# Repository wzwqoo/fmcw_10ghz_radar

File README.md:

# 10 GHz FMCW Radar Sensing Platform

A single-board **1TX / 3RX, 10 GHz FMCW radar**, its **Artix-7 range–Doppler–CFAR
backend**, and the **carrier board** that mounts the radar alongside a
pair of global-shutter cameras and an impact microphone.

The target application is a golf launch monitor: recover a ball's speed, launch
direction, spin rate and spin axis from radar and camera data. That
application drives every architectural choice here — three non-collinear
receivers (the minimum that gives a radar-native spin axis), per-receiver
*complex* range–Doppler maps published to DDR3 (the phase the spin-axis
interferometer consumes), and a once-per-shot Ethernet offload so the heavy
post-processing runs on a host PC instead of in fabric.

## Repository structure

| Path | Subsystem |
|---|---|
| [`rf_frontend/`](rf_frontend/) | The 10 GHz 1TX/3RX FMCW front-end: KiCad schematics and PCB on Isola 370HR |
| [`fpga/`](fpga/) | Artix-7 gateware: the raw-ADC → range–Doppler → CFAR pipeline, the DDR-to-host UDP offload path, MicroBlaze firmware, and the simulation stack |
| [`carrier_board/`](carrier_board/) | The carrier PCB that ties two cameras, radar, the FPGA module, Ethernet and audio together |

Each subsystem has its own README with the detail; the tables below are the map.

### `rf_frontend/` — 10 GHz FMCW front-end

A closed-loop fractional-N ramp PLL (ADF4159) drives a 10 GHz VCO (HMC1163)
across a 192 MHz sweep in 108 µs. A branchline coupler and a 3-way Wilkinson
tree supply a coherent LO to three
LNA-first receive chains (PMA3-14LN+ → LTC5548 → ADA4940-2), which land on an
ADAR7251's simultaneously-sampled channels. The antennas are series-fed patch
columns arranged in a staggered "^", stepped λ/2 between adjacent phase centres
in both array axes, so per-Doppler-bin angles never wrap.

→ [`rf_frontend/README.md`](rf_frontend/README.md)

### `fpga/` — Artix-7 digital backend

`01_adar7251_ppi_rx` → TDM mux → band-pass + Hilbert FIR → per-RX range FFT →
transposed DDR scatter (region A) → Doppler sequencer → per-RX Doppler FFT →
non-coherent integration (region C) + per-RX complex cache (region B) →
streaming cell-averaging CFAR (region D). A 128 × 256 grid, double-buffered so
software never reads a torn frame. An audio-plus-speed trigger picks the first
frame after impact that clears both gates and dumps its B/C/D regions to the
host over UDP.

→ [`fpga/README.md`](fpga/README.md)

### `carrier_board/` — camera + radar carrier

The routed six-layer carrier connects two OV9281 cameras through MC20901
bridges, the radar through a 40-pin FPC, and the Artix-7 module through two
140-pin B2B connectors. It also carries I²S audio, Gigabit Ethernet, and the
power tree.

→ [`carrier_board/README.md`](carrier_board/README.md)

## Status

| Item | State |
|---|---|
| `rf_frontend/` schematics + PCB layout | Routed KiCad project; board validation remains open |
| `fpga/` RTL pipeline (`01`…`08`) | Complete; unit tests and a raw-ADC-to-CFAR xsim run against the real Xilinx FFT/FIR IP |
| `fpga/` host offload (streamer, packetizer, receiver) | Complete and unit-tested |
| `fpga/firmware/audio_dsp.c` | Complete |
| `fpga/firmware/fusion_control.c` | **Work in progress** — the audio + speed trigger FSM and its frame-selection policy are still being written |
| `carrier_board/ov9281/` | Routed KiCad project; camera fit and board bring-up remain open |

## Toolchain

| Tool | Used for |
|---|---|
| KiCad 10 | `rf_frontend/kicad/`, `carrier_board/ov9281/` |
| Vivado 2025.1 | Block design, IP generation, synthesis, the xsim end-to-end run |
| Icarus Verilog | The RTL unit tests — they need no vendor IP (`fpga/sim/run_unit_tests.sh`) |
| Python 3 (numpy, matplotlib) | Stimulus generation, CFAR golden checks, the UDP frame receiver |
| FreeCAD | Archived IMX477 lens holder in `carrier_board/archive/imx477/mechanical/` |

Large generated trees are deliberately out of the repository: the Vivado
project's `.runs`/`.gen`/`.cache` output, xsim build directories, and the ADS
and HFSS workspaces.

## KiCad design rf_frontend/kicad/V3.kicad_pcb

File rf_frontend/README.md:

# `rf_frontend/` — 10 GHz 1TX/3RX FMCW front-end

The analog half of the platform: a coherent FMCW radar that sweeps 192 MHz
around 10 GHz in 108 µs, radiates it from a series-fed patch column, and lands
three receive chains on an ADAR7251's simultaneously-sampled ADC channels.
Simultaneous sampling is the point — it is what preserves the inter-receiver
phase that angle-of-arrival and the spin-axis interferometer downstream consume.

Everything is discrete MMIC rather than an integrated transceiver, so each
channel's gain, noise figure and LO drive is set and measurable on its own.

## Signal chain

## Key components

| Function | Part |
|---|---|
| Ramp PLL (fractional-N, type 2) | ADF4159 |
| VCO, 10 GHz fundamental + ÷2 | HMC1163 |
| Loop-filter amplifier (JFET input) | ADA4625-1 |
| Reference oscillator / buffer | KT2520K, NB3N551 |
| LNA, ×3 | PMA3-14LN+ |
| Downconversion mixer, ×3 | LTC5548 |
| Differential IF driver | ADA4940-2 |
| ADC — 4 channels, simultaneous sampling | ADAR7251 |
| LO distribution | LO-favor branchline coupler + 3-way Wilkinson with two 75 Ω isolation resistors + phase-trimmed arms (all distributed, on-board) |
| Pad attenuators | PAT1220 (4 dB / 6 dB) |
| Supplies | TPS7A4701 and TPS7A91 (low-noise LDO for the RF rails), TPS54302, MIC29302A, ADP1613 boost |
| Host interface | 40-pin shielded FPC to the carrier board |

## Antenna array

Three receive columns and one transmit column use series-fed patches on the
top layer. Ground cutouts and stitched feed transitions connect the columns
to the RF front-end.

## Substrate

Four-layer Isola 370HR, with the RF routing referenced to In1 and the antenna
columns over In2.

## Layout

| Path | Contents |
|---|---|
| `kicad/V3.kicad_pro`, `V3.kicad_sch` | KiCad project and top-level sheet |
| `kicad/TX.kicad_sch` | VCO, ramp PLL, loop filter, coupler, LO tree, TX feed |
| `kicad/RX.kicad_sch` | 3× LNA → mixer receive chains |
| `kicad/IF.kicad_sch` | IF conditioning and the ADAR7251 |
| `kicad/power.kicad_sch` | Power tree, with the RF rails on low-noise LDOs |
| `kicad/V3.kicad_pcb`, `V3.kicad_dru` | Board layout and custom DRC rules (net classes, input-path width) |
| `kicad/Design1.pll`, `Design2.pll` | ADIsimPLL loop designs |
| `kicad/footprints/` | Project-local libraries — including the hand-drawn `antenna`, `splitter` and `branchline` distributed structures |
| `figures/` | Link budget and board render |

The distributed structures are *footprints*, not components: the patch column,
the Wilkinson splitter and the branchline coupler are drawn as copper in
`kicad/footprints/*.pretty` and placed like parts.

## Status

The routed KiCad design is included. Board validation remains open.

## Opening the board

```
kicad rf_frontend/kicad/V3.kicad_pro     # KiCad 10
```

The render at the top of this page was produced with `kicad-cli pcb render`.

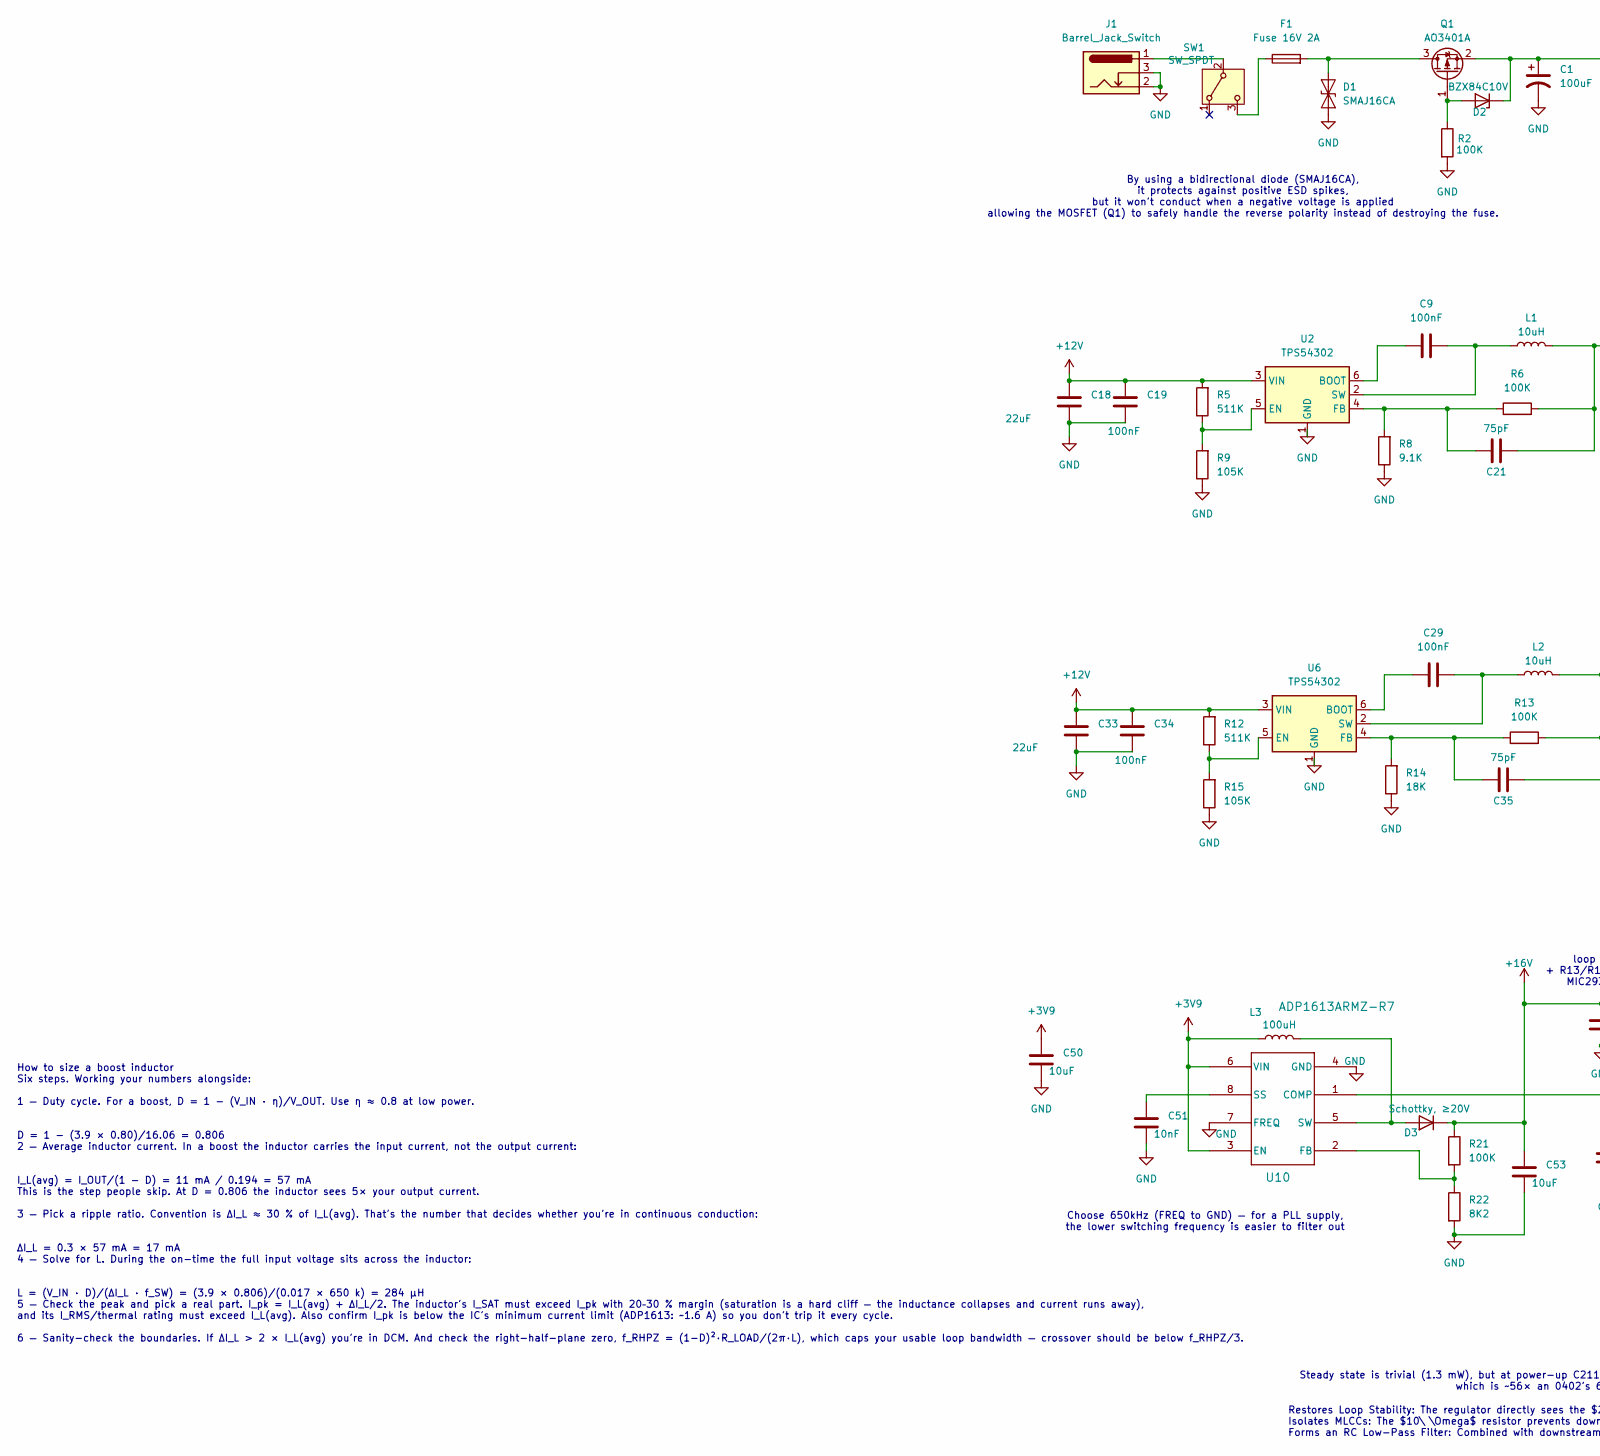
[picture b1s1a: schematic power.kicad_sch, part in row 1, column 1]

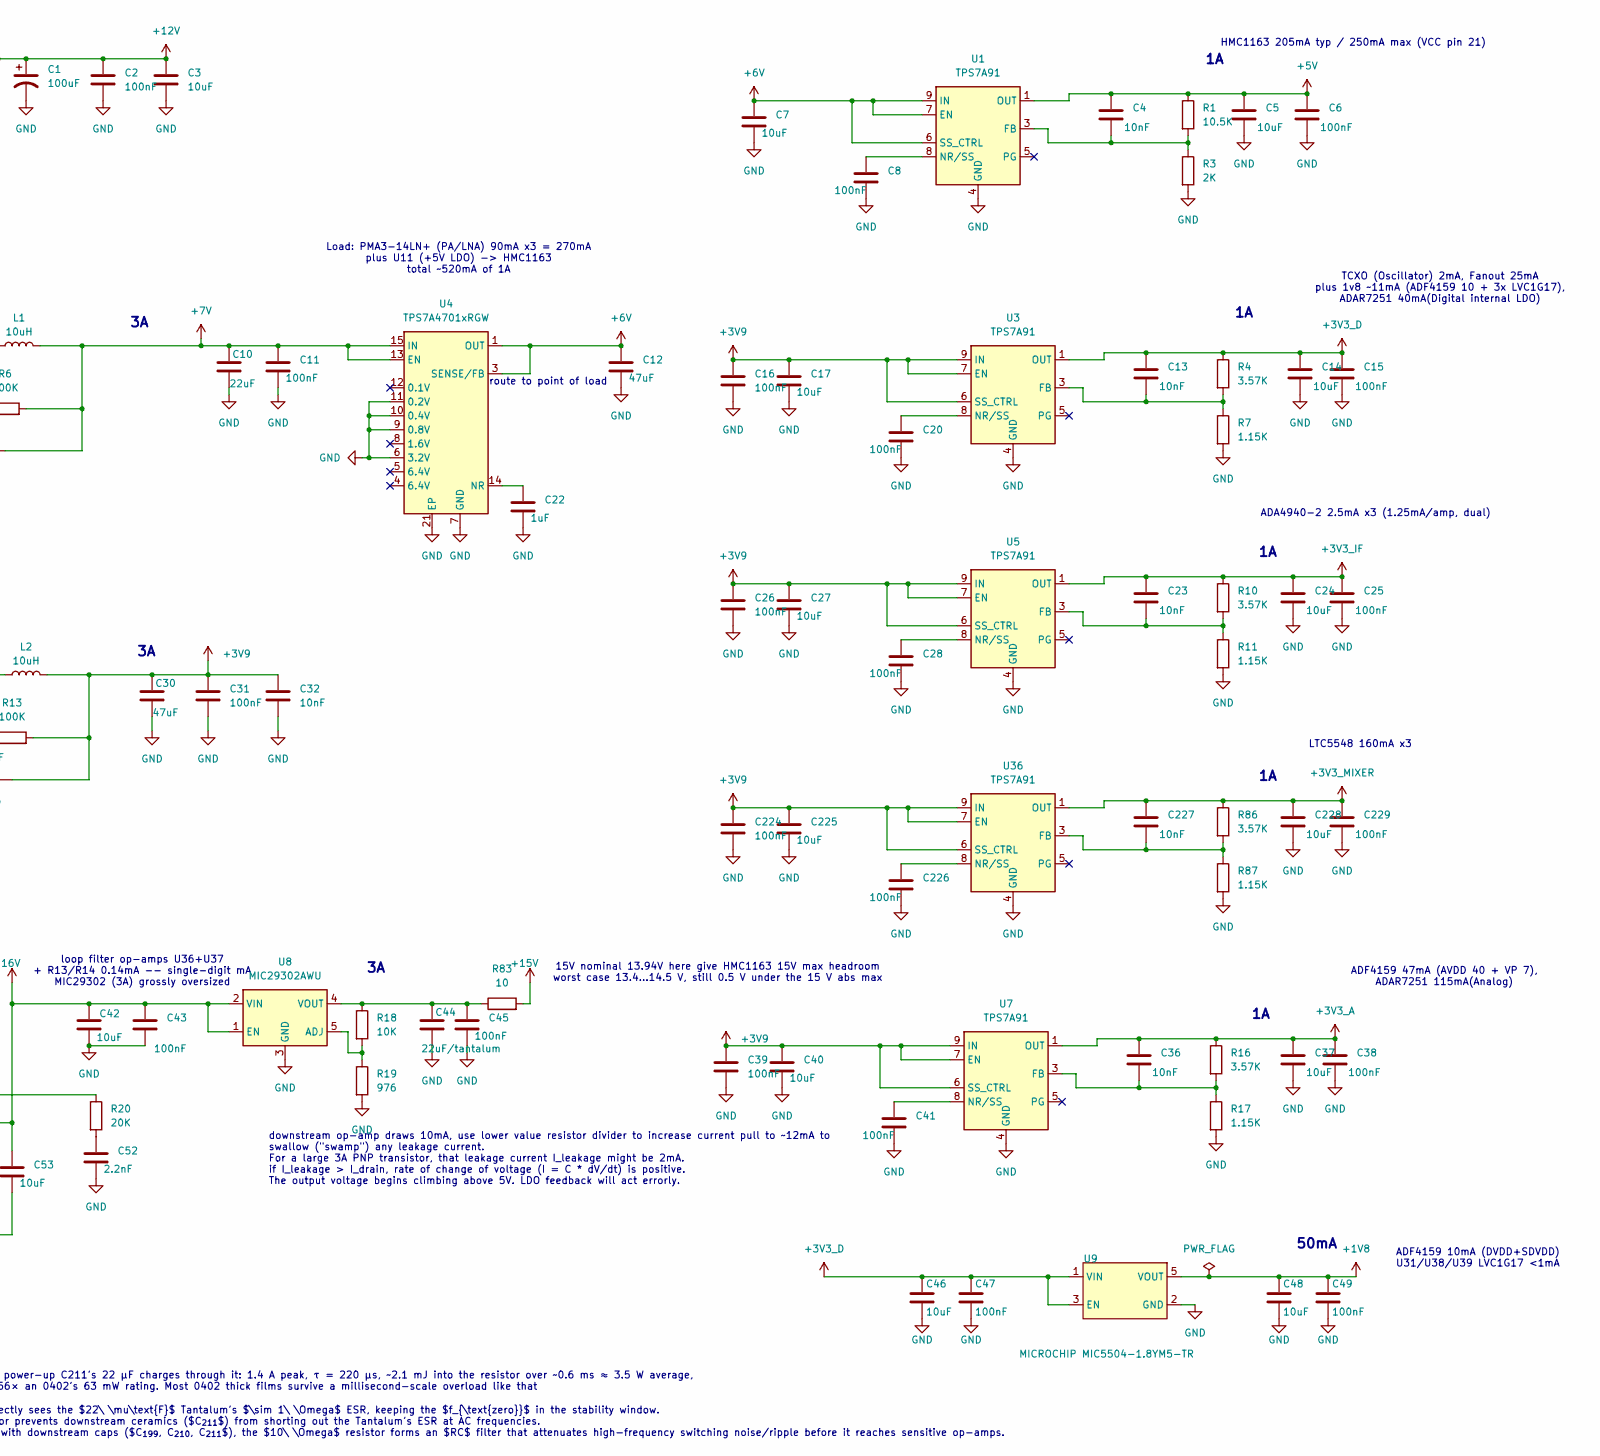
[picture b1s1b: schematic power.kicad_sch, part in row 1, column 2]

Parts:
C1: 100uF; CAPC6153X670N
C2, C6, C8, C9, C11, C15, C16, C19, C20, C25, C26, C28, C29, C31, C34, C38, C39, C41, C43, C45, C47, C49, C224, C226, C229: 100nF; C_0402_1005Metric
C3, C5, C7, C14, C17, C24, C27, C37, C40, C42, C46, C48, C50, C53, C225, C228: 10uF; C_0805_2012Metric
C4, C13, C23, C32, C36, C51, C227: 10nF; C_0402_1005Metric
C10, C18, C33: 22uF; C_0805_2012Metric
C12, C30: 47uF; C_0805_2012Metric
C21, C35: 75pF; C_0402_1005Metric
C22: 1uF; C_0402_1005Metric
C44: 22uF/tantalum; CP_EIA-6032-28_Kemet-C
C52: 2.2nF; C_0402_1005Metric
D1: SMAJ16CA; D_SMA
D2: BZX84C10V; SOT-23
D3: Schottky, ≥20V; D_SMA
F1: Fuse 16V 2A; Fuse_1812_4532Metric; LCSC Part # SMD1812P200TF16
J1: Barrel_Jack_Switch; BarrelJack_CUI_PJ-063AH_Horizontal
L1, L2: 10uH; L_Sunlord_MWSA0602S; Part# FXL0630-100-M
L3: 100uH; L_TechFuse_SL0620
Q1: AO3401A; SOT-23
R1: 10.5K; R_0402_1005Metric
R2, R6, R13, R21: 100K; R_0402_1005Metric
R3: 2K; R_0402_1005Metric
R4, R10, R16, R86: 3.57K; R_0402_1005Metric
R5, R12: 511K; R_0402_1005Metric
R7, R11, R17, R87: 1.15K; R_0402_1005Metric
R8: 9.1K; R_0402_1005Metric
R9, R15: 105K; R_0402_1005Metric
R14: 18K; R_0402_1005Metric
R18: 10K; R_0402_1005Metric
R19: 976; R_0402_1005Metric
R20: 20K; R_0402_1005Metric
R22: 8K2; R_0402_1005Metric
R83: 10; R_0603_1608Metric
SW1: SW_SPDT; SW-TH_3P-L12.7-W6.6-P4.70_C9900034369; Part# SS-12D10-G090; LCSC Part # C5155552
U1, U3, U5, U7, U36: TPS7A91; Texas_S-PDSO-N10_EP1.2x2mm
U2, U6: TPS54302; SOT-23-6
U4: TPS7A4701xRGW; Texas_RGW0020A_VQFN-20-1EP_5x5mm_P0.65mm_EP3.15x3.15mm
U8: MIC29302AWU; TO-263-5_TabPin3
U9: MICROCHIP MIC5504-1.8YM5-TR; SOT-23-5; Part# MIC5504-1.8YM5-TR; LCSC Part # C626116
U10: ADP1613ARMZ-R7; MSOP-8-1EP_3x3mm_P0.65mm_EP1.5x1.8mm

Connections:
+1V8: C48.1, C49.1, U9.5 (VOUT); also elsewhere on the board
+3V3_A: C36.1, C37.1, C38.1, R16.1, U7.1 (OUT), U7.2 (OUT); also elsewhere on the board
+3V3_D: C13.1, C14.1, C15.1, C46.1, C47.1, R4.1, U3.1 (OUT), U3.2 (OUT), U9.1 (VIN), U9.3 (EN); also elsewhere on the board
+3V3_IF: C23.1, C24.1, C25.1, R10.1, U5.1 (OUT), U5.2 (OUT); also elsewhere on the board
+3V3_MIXER: C227.1, C228.1, C229.1, R86.1, U36.1 (OUT), U36.2 (OUT); also elsewhere on the board
+3V9: C16.1, C17.1, C26.1, C27.1, C30.1, C31.1, C32.1, C35.2, C39.1, C40.1, C50.1, C224.1, C225.1, L2.2, L3.1, R13.2, U3.6 (SS_CTRL), U3.7 (EN), U3.9 (IN), U3.10 (IN), U5.6 (SS_CTRL), U5.7 (EN), U5.9 (IN), U5.10 (IN), U7.6 (SS_CTRL), U7.7 (EN), U7.9 (IN), U7.10 (IN), U10.3 (EN), U10.6 (VIN), U36.6 (SS_CTRL), U36.7 (EN), U36.9 (IN), U36.10 (IN)
+5V: C4.1, C5.1, C6.1, R1.1, U1.1 (OUT), U1.2 (OUT); also elsewhere on the board
+6V: C7.1, C12.1, U1.6 (SS_CTRL), U1.7 (EN), U1.9 (IN), U1.10 (IN), U4.1 (OUT), U4.3 (SENSE/FB), U4.20 (OUT); also elsewhere on the board
+7V: C10.1, C11.1, C21.2, L1.2, R6.2, U4.13 (EN), U4.15 (IN), U4.16 (IN)
+12V: C1.1, C2.1, C3.1, C18.1, C19.1, C33.1, C34.1, D2.3 (K), Q1.2 (S), R5.2, R12.2, U2.3 (VIN), U6.3 (VIN)
+15V: R83.2; also elsewhere on the board
+16V: C42.1, C43.1, C53.1, D3.1 (K), R21.1, U8.1 (EN), U8.2 (VIN)
GND: C1.2, C2.2, C3.2, C5.2, C6.2, C7.2, C8.2, C10.2, C11.2, C12.2, C14.2, C15.2, C16.2, C17.2, C18.2, C19.2, C20.2, C22.2, C24.2, C25.2, C26.2, C27.2, C28.2, C30.2, C31.2, C32.2, C33.2, C34.2, C37.2, C38.2, C39.2, C40.2, C41.2, C42.2, C43.2, C44.2, C45.2, C46.2, C47.2, C48.2, C49.2, C50.2, C51.2, C52.2, C53.2, C224.2, C225.2, C226.2, C228.2, C229.2, D1.1 (A1), J1.2, J1.3, R2.2, R3.2, R7.2, R8.1, R9.1, R11.2, R14.1, R15.1, R17.2, R19.2, R22.2, R87.2, U1.4 (GND), U1.11 (GND), U2.1 (GND), U3.4 (GND), U3.11 (GND), U4.6 (3.2V), U4.7 (GND), U4.9 (0.8V), U4.10 (0.4V), U4.11 (0.2V), U4.21 (EP), U5.4 (GND), U5.11 (GND), U6.1 (GND), U7.4 (GND), U7.11 (GND), U8.3 (GND), U9.2 (GND), U10.4 (GND), U10.7 (FREQ), U10.9 (EP), U36.4 (GND), U36.11 (GND); also elsewhere on the board
unnamed: C52.1, R20.2
unnamed: D1.2 (A2), F1.2, Q1.3 (D)
unnamed: D2.1 (A), Q1.1 (G), R2.1
unnamed: D3.2 (A), L3.2, U10.5 (SW)
unnamed: J1.1, SW1.2 (B)
unnamed: F1.1, SW1.3 (C)
unnamed: C4.2, R1.2, R3.1, U1.3 (FB)
unnamed: C8.1, U1.8 (NR/SS)
unnamed: C9.1, U2.6 (BOOT)
unnamed: R5.1, R9.2, U2.5 (EN)
unnamed: C21.1, R6.1, R8.2, U2.4 (FB)
unnamed: C9.2, L1.1, U2.2 (SW)
unnamed: C13.2, R4.2, R7.1, U3.3 (FB)
unnamed: C20.1, U3.8 (NR/SS)
unnamed: C22.1, U4.14 (NR)
unnamed: C23.2, R10.2, R11.1, U5.3 (FB)
unnamed: C28.1, U5.8 (NR/SS)
unnamed: C29.1, U6.6 (BOOT)
unnamed: R12.1, R15.2, U6.5 (EN)
unnamed: C35.1, R13.1, R14.2, U6.4 (FB)
unnamed: C29.2, L2.1, U6.2 (SW)
unnamed: C36.2, R16.2, R17.1, U7.3 (FB)
unnamed: C41.1, U7.8 (NR/SS)
unnamed: R18.2, R19.1, U8.5 (ADJ)
unnamed: C44.1, C45.1, R18.1, R83.1, U8.4 (VOUT)
unnamed: R20.1, U10.1 (COMP)
unnamed: R21.2, R22.1, U10.2 (FB)
unnamed: C51.1, U10.8 (SS)
unnamed: C227.2, R86.2, R87.1, U36.3 (FB)
unnamed: C226.1, U36.8 (NR/SS)

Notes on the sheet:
Steady state is trivial (1.3 mW), but at power-up C211's 22 µF charges through it: 1.4 A peak, τ = 220 µs, ~2.1 mJ into the resistor over ~0.6 ms ≈ 3.5 W average, which is ~56× an 0402's 63 mW rating. Most 0402 thick films survive a millisecond-scale overload like that
By using a bidirectional diode (SMAJ16CA), it protects against positive ESD spikes, but it won't conduct when a negative voltage is applied allowing the MOSFET (Q1) to safely handle the reverse polarity instead of destroying the fuse.
ADF4159 10mA (DVDD+SDVDD) U31/U38/U39 LVC1G17 <1mA
route to point of load
TCXO (Oscillator) 2mA, Fanout 25mA plus 1v8 ~11mA (ADF4159 10 + 3x LVC1G17), ADAR7251 40mA(Digital internal LDO)
downstream op-amp draws 10mA, use lower value resistor divider to increase current pull to ~12mA to swallow ("swamp") any leakage current. For a large 3A PNP transistor, that leakage current I_leakage might be 2mA. if I_leakage > I_drain, rate of change of voltage (I = C * dV/dt) is positive. The o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
How to size a boost inductor Six steps. Working your numbers alongside: 1 — Duty cycle. For a boost, D = 1 − (V_IN · η)/V_OUT. Use η ≈ 0.8 at low power. D = 1 − (3.9 × 0.80)/16.06 = 0.806 2 — Average inductor current. In a boost the inductor carries the input current, not the output current: I_L(av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
Load: PMA3-14LN+ (PA/LNA) 90mA x3 = 270mA plus U11 (+5V LDO) -> HMC1163 total ~520mA of 1A
50mA
loop filter op-amps U36+U37 + R13/R14 0.14mA -- single-digit mA MIC29302 (3A) grossly oversized
15V nominal 13.94V here give HMC1163 15V max headroom worst case 13.4…14.5 V, still 0.5 V under the 15 V abs max
LTC5548 160mA x3
ADA4940-2 2.5mA x3 (1.25mA/amp, dual)
Restores Loop Stability: The regulator directly sees the $22\ \mu\text{F}$ Tantalum's $\sim 1\ \Omega$ ESR, keeping the $f_{\text{zero}}$ in the stability window. Isolates MLCCs: The $10\ \Omega$ resistor prevents downstream ceramics ($C_{211}$) from shorting out the Tantalum's ESR at AC frequencie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
Choose 650kHz (FREQ to GND) — for a PLL supply, the lower switching frequency is easier to filter out
ADF4159 47mA (AVDD 40 + VP 7), ADAR7251 115mA(Analog)
HMC1163 205mA typ / 250mA max (VCC pin 21)
